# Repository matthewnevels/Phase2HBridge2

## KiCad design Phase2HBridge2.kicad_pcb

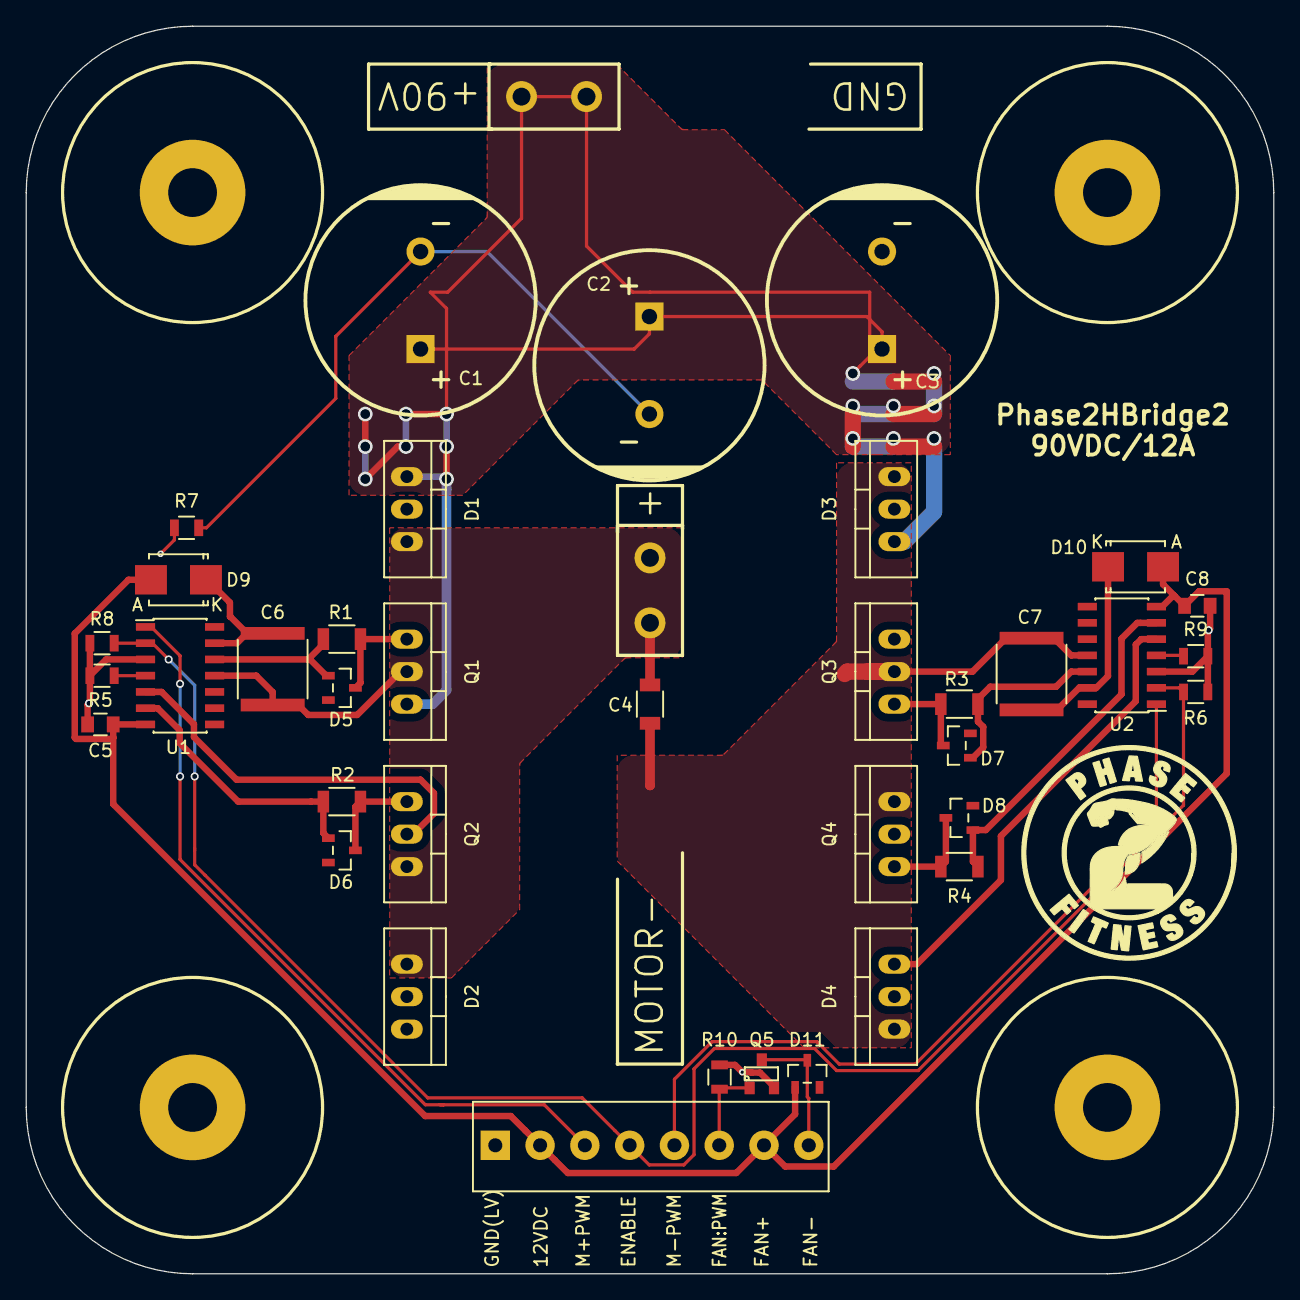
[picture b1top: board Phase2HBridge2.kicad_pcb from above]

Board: 2 copper layers, 97.5 x 97.5 mm, 43 parts (0 on the bottom side), 23 nets.

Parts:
C1, C2, C3: CAP-ALUM-220uF-200V-20%-EEU-ED2D221; Capacitor18x31.5RM7.5
C4: CAP-CER-470pF-630V-5%-NPO-1206-C1206C471JBGACTU; C_1206
C5, C8: CAP-CER-0.1uF-50V-10%-X7R-0805-C0805C104K5RACAUTO; C_0805
C6, C7: CAP-CER-0.68uF-250V-10%-X7R-2220-C2220C684KARACTU; C_2220
D1, D2, D3, D4: DIODE-SCH-250V-40A-MBR40250; TO-220_Neutral123_Vertical
D5, D6, D7, D8, D11: DIODE-SCH-40V-750mA-BAT750; sot23
D9, D10: DIODE-SCH-200V-3A-MBRS3200T3G; Diode-SMB_Standard
H1, H2, H3, H4: MountingHole-#6-Conductive
J1: CONN-01X08-TerminalBlock-3.5mm-Side-1776275-8; CON-TerminalBlock-8Pos-Side-3.5MM-1776275-8
J2, J4: CONN-FASTON-0.250; CON-FASTON-0.250-1217861-1
Q1, Q2, Q3, Q4: FET-NCH-400V-26A-TO220-FDP26N40; TO-220_Neutral123_Vertical
Q5: BSS138; SOT-23
R1, R2, R3, R4: RES-4.7-.25W-1%-1206-CRCW12064R70FKEA; R_1206
R5, R6, R10: RES-10k-.125W-1%-0805-ERJ-6ENF1002V; R_0805
R7, R8, R9: RES-0.0-.125W-0805-ERJ-6GEY0R00V; R_0805
U1, U2: IC-Driver-HalfBridge-FAN7393AMX; SOIC-14_3.9x8.7mm_Pitch1.27mm

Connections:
/DT_M+: R8.2, U1.4
/DT_M-: R9.1, U2.4
/G_HI_M+: D5.3, Q1.1, R1.1
/G_HI_M-: D7.3, Q3.1, R3.2
/G_LO_M+: D6.3, Q2.1, R2.1
/G_LO_M-: D8.3, Q4.1, R4.2
/HO_M+: D5.1, R1.2, U1.12
/HO_M-: D7.1, R3.1, U2.12
/LO_M+: D6.1, R2.2, U1.6
/LO_M-: D8.1, R4.1, U2.6
/MOTOR+: C4.2, C6.1, D1.3, D2.1, Q1.2, Q2.3, U1.11
/MOTOR-: C4.1, C7.2, D3.3, D4.1, J4.1, Q3.2, Q4.3, U2.11
/Vb_M+: C6.2, D9.2, U1.13
/Vb_M-: C7.1, D10.2, U2.13
ENABLE: J1.4, R5.1, R6.1, U1.2, U2.2
FAN-: D11.3, J1.8, Q5.3
GND: C1.2, C2.2, C3.2, D2.3, D4.3, J2.1, Q2.2, Q4.2, R7.2, U1.5, U2.5
PWM_FAN: J1.6, Q5.1, R10.1
PWM_M+: J1.3, U1.1
PWM_M-: J1.5, U2.1
VDD: C5.2, C8.1, D9.1, D10.1, D11.1, J1.2, J1.7, U1.7, U2.7
VPP: C1.1, C2.1, C3.1, D1.1, D3.1, Q1.3, Q3.3
VSS: C5.1, C8.2, J1.1, Q5.2, R5.2, R6.2, R7.1, R8.1, R9.2, R10.2, U1.3, U2.3

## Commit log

2015-02-09 Initial Commit
    Schematic is ready for review
2015-02-09 PCB Started
2015-02-10 Parts Placed - Need to Route
2015-02-12 Finished Layout
    Need to Verify Layout, add graphics, update refused locations, etc…
2015-03-11 Finished Design
2015-03-11 Final Commit
